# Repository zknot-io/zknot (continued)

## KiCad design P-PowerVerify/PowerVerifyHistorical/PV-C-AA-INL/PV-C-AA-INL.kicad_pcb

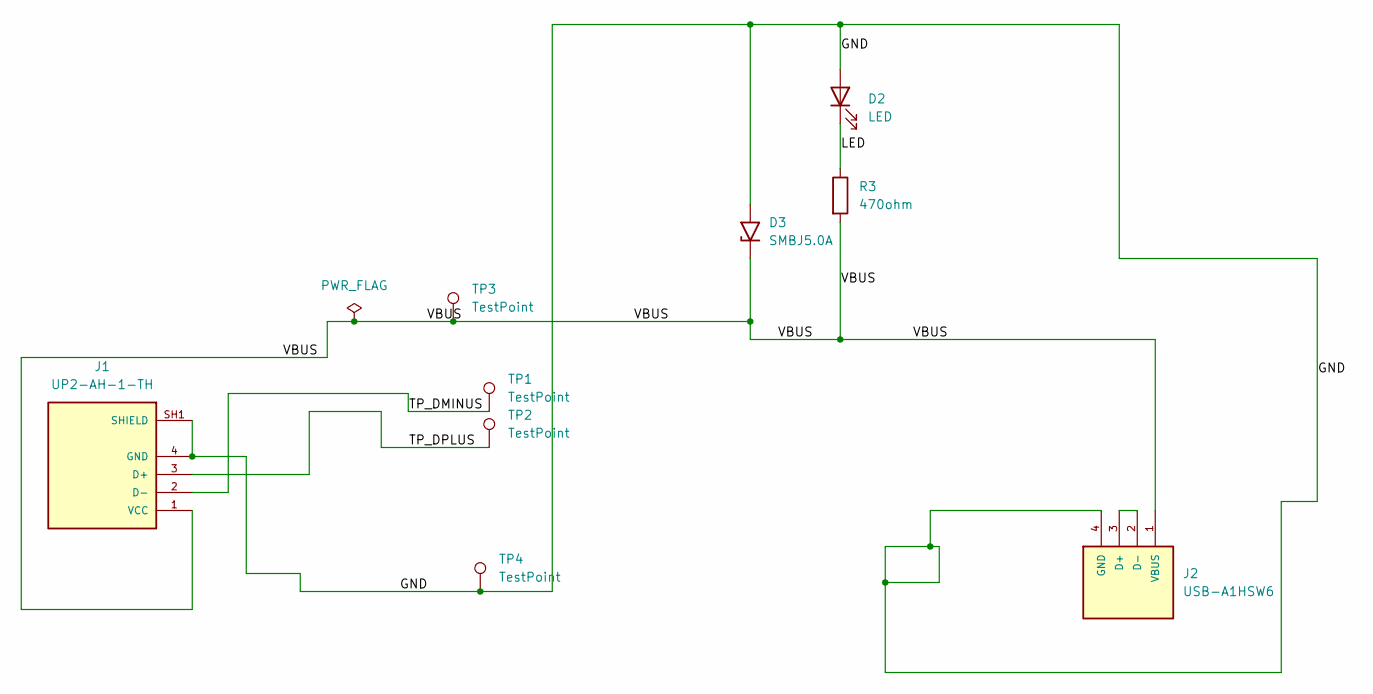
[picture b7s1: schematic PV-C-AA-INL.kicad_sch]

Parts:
D2: LED; LED_0603_1608Metric
D3: SMBJ5.0A; D_SMB
J1: UP2-AH-1-TH; CUI_UP2-AH-1-TH; PARTREV 1.05; DigiKey_Part_Number 102-3996-ND
J2: USB-A1HSW6; OST_USB-A1HSW6; PARTREV A; DigiKey_Part_Number ED2989-ND
R3: 470ohm; R_0402_1005Metric
TP1, TP2, TP3, TP4: TestPoint; TestPoint_Pad_D1.5mm

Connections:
/GND: D2.2 (A), D3.2 (A2), J1.4 (GND), J1.SH1 (SHIELD), J1.SH2 (SHIELD), J2.4 (GND), TP4.1
/LED: D2.1 (K), R3.1
/TP_DMINUS: J1.2 (D-), TP1.1
/TP_DPLUS: J1.3 (D+), TP2.1
/VBUS: D3.1 (A1), J1.1 (VCC), J2.1 (VBUS), R3.2, TP3.1
unnamed: J2.2 (D-), J2.3 (D+)

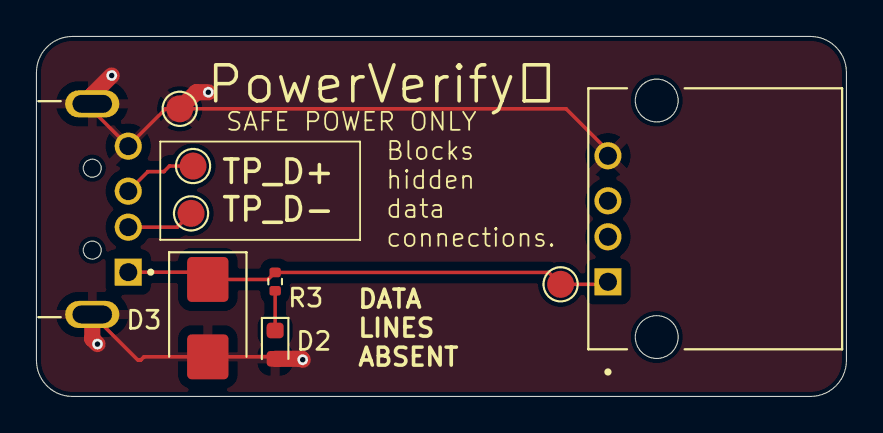
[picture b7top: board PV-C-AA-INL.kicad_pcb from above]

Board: 2 copper layers, 45.0 x 20.0 mm, 9 parts (0 on the bottom side), 6 nets.

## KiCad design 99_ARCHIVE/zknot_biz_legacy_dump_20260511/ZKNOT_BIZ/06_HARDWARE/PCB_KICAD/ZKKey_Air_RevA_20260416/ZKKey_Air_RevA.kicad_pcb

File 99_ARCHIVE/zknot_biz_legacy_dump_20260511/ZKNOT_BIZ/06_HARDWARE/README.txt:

ZKNOT / 06_HARDWARE
====================
Hardware design files, BOMs, and hardware master documents.

SUBFOLDERS:
  PCB_KICAD/  — KiCad project files (.zip per board revision)
  GERBERS/    — Fabrication Gerber files (.zip per board revision)
  BOM/        — Bills of materials (.xlsx)
  HW_DOCS/    — Hardware master documents (.docx)

CANONICAL FILES:
  ZKNOT_BOM-001_ZKM001_assembly_kit_20260301.xlsx
  ZKNOT_HW-001_ZKM001_hardware_firmware_master_20260301.docx
  ZKNOT_PCB-001_ZKM001_kicad_project_20260301.zip
  ZKNOT_PCB-001_ZKM001_gerbers_20260301.zip
  ZKNOT_PCB-002_PowerVerify_RevE_kicad_project_20260301.zip
  ZKNOT_PCB-002_PowerVerify_RevE_gerbers_20260301.zip
  ZKNOT_BOM-002_PowerVerify_RevE_bom_20260301.xlsx
  ZKNOT_DOC-010_device_id_registry_20260301.xlsx
  ZKNOT_HW-002_ZKKeyConnect_build1_wiring_doc_20260301.docx

TYPE CODES: BOM, HW, PCB

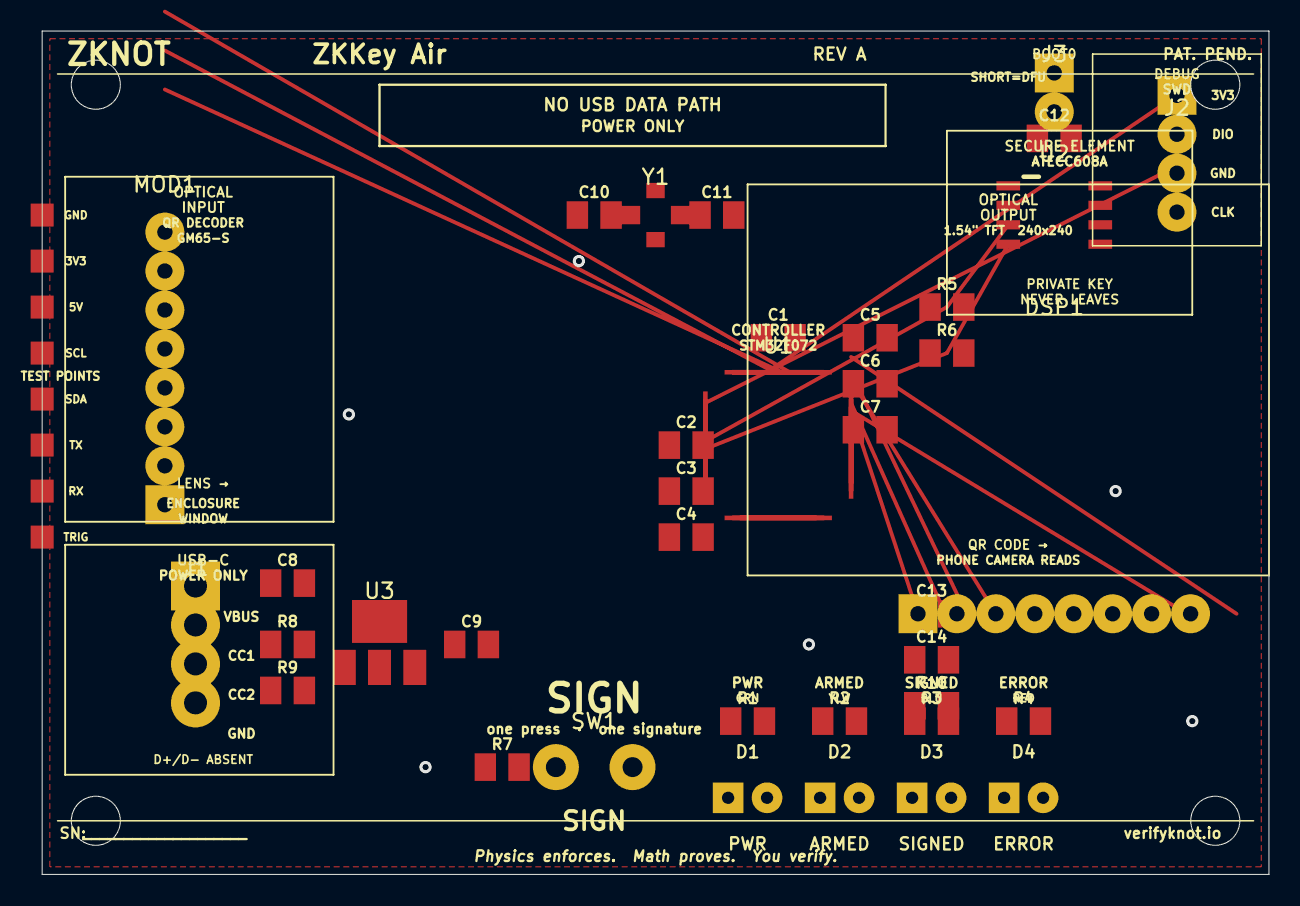
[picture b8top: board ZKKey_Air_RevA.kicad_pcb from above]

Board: 2 copper layers, 80.0 x 55.0 mm, 38 parts (0 on the bottom side), 26 nets.

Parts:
C1, C2, C3, C4, C5, C6, C7, C8, C9, C10, C11, C12, C13, C14: C_0805_2012Metric
D1: PWR; LED_D3.0mm
D2: ARMED; LED_D3.0mm
D3: SIGNED; LED_D3.0mm
D4: ERROR; LED_D3.0mm
DSP1: ST7789 TFT; PinHeader_1x08_P2.54mm_Vertical
J1: USB-C_PWR_ONLY; PinHeader_1x04_P2.54mm_Vertical
J2: SWD; PinHeader_1x04_P2.54mm_Vertical
J3: PinHeader_1x02_P2.54mm_Vertical
MOD1: GM65-S; PinHeader_1x08_P2.54mm_Vertical
R1, R2, R3, R4, R5, R6, R7, R8, R9, R10: R_0805_2012Metric
SW1: SIGN; SW_Tactile_SPST_Angled_PTS645
U1: STM32F072CBT6; LQFP-48_7x7mm_P0.5mm
U2: ATECC608A; SOIC-8_3.9x4.9mm_P1.27mm
U3: AMS1117-3.3; SOT-223-3_TabPin2
Y1: Crystal_SMD_3225-4Pin_3.2x2.5mm

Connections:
+3.3V: C2.1, C3.1, C4.1, C5.1, C6.1, C7.1, C9.1, C12.1, C13.1, C14.1, DSP1.2, J2.1, J3.2, MOD1.1, R5.1, R6.1, U1.1, U1.2, U1.9, U1.24, U1.48, U2.8, U3.2
+5V: C8.1, U3.3
ATEC_ALERT: U1.39, U2.2
BOOT0: J3.1, U1.44
BTN_PA0: R7.1, SW1.1, U1.10
CC1_5V1K: J1.2, R8.1
CC2_5V1K: J1.3, R9.1
GM65_TRIG: MOD1.5, U1.29
GND: C1.2, C2.2, C3.2, C4.2, C5.2, C6.2, C7.2, C8.2, C9.2, C10.2, C11.2, C12.2, C13.2, C14.2, D1.1, D2.1, D3.1, D4.1, DSP1.1, J1.4, J2.3, MOD1.2, R7.2, R8.2, R9.2, SW1.2, U1.8, U1.23, U1.47, U2.3, U3.1, Y1.3, Y1.4
I2C_SCL: R5.2, U1.42, U2.7
I2C_SDA: R6.2, U1.43, U2.5
LED_ARMED_PA2: D2.2, R2.1, R2.2, U1.12
LED_ERROR_PA6: D4.2, R4.1, R4.2, U1.16
LED_PWR_PA1: D1.2, R1.1, R1.2, U1.11
LED_SIGNED_PA3: D3.2, R3.1, R3.2, U1.13
NRST: C1.1, U1.7
SPI_MOSI: DSP1.4, U1.17
SPI_SCK: DSP1.3, U1.15
SWCLK: J2.4, U1.37
SWDIO: J2.2, U1.34
TFT_BL: DSP1.8, R10.1, R10.2, U1.21
TFT_CS: DSP1.7, U1.14
TFT_DC: DSP1.6, U1.26
TFT_RST: DSP1.5, U1.27
UART_RX: MOD1.3, U1.31
UART_TX: MOD1.4, U1.30

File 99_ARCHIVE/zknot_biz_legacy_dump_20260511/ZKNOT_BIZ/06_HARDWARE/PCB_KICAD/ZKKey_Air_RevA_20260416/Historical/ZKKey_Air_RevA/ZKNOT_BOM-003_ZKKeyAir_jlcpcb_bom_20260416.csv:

Comment,Designator,Footprint,LCSC Part #,Qty,Assembly,Notes
STM32F072CBT6,U1,Package_QFP:LQFP-48_7x7mm_P0.5mm,C81720,1,SMT,Reflow — same as Connect
ATECC608A-MAHDA-T,U2,Package_SO:SOIC-8_3.9x4.9mm_P1.27mm,C3395330,1,SMT,Reflow — same as Connect
AMS1117-3.3,U3,Package_TO_SOT_SMD:SOT-223-3_TabPin2,C6186,1,SMT,Reflow — 3.3V LDO
Crystal 8MHz,Y1,Crystal:Crystal_SMD_3225-4Pin_3.2x2.5mm,C9002,1,SMT,Reflow — HSE oscillator
100nF 0805,C1 C3 C4 C5 C12 C14,Capacitor_SMD:C_0805_2012Metric,C49678,6,SMT,Decoupling
10uF 0805,C2 C8 C9 C13,Capacitor_SMD:C_0805_2012Metric,C17024,4,SMT,Bulk decoupling — LDO and TFT
1uF 0805,C6,Capacitor_SMD:C_0805_2012Metric,C15849,1,SMT,VDDA bulk
10nF 0805,C7,Capacitor_SMD:C_0805_2012Metric,C57112,1,SMT,VDDA HF
12pF 0805,C10 C11,Capacitor_SMD:C_0805_2012Metric,C1557,2,SMT,Crystal load caps
270R 0805,R1 R2 R3 R4,Resistor_SMD:R_0805_2012Metric,C17630,4,SMT,LED current limit 270Ω
4.7k 0805,R5 R6,Resistor_SMD:R_0805_2012Metric,C23162,2,SMT,I2C pull-ups
10k 0805,R7,Resistor_SMD:R_0805_2012Metric,C17414,1,SMT,Button pull-down
5.1k 0805,R8 R9,Resistor_SMD:R_0805_2012Metric,C23186,2,SMT,USB-C CC1/CC2 pull-downs
10R 0805,R10,Resistor_SMD:R_0805_2012Metric,C17561,1,SMT,TFT backlight current limit
GM65-S QR Decoder Module,MOD1,Connector_PinHeader_2.54mm:PinHeader_1x08_P2.54mm_Vertical,,1,THT,Source: Handheld Scientific GM65-S or Grow GM65 — UART 3.3V — 30x17mm module — mount lens toward enclosure window
ST7789 1.54in 240x240 TFT,DSP1,Connector_PinHeader_2.54mm:PinHeader_1x08_P2.54mm_Vertical,,1,THT,Source: AliExpress/Adafruit 1.54in 240x240 SPI ST7789 module — GND VCC SCL SDA RES DC CS BL pinout — display face up through enclosure window
LED 3mm Green,D1,LED_THT:LED_D3.0mm,,1,THT,PWR — source locally
LED 3mm Yellow,D2,LED_THT:LED_D3.0mm,,1,THT,ARMED — source locally
LED 3mm Blue,D3,LED_THT:LED_D3.0mm,,1,THT,SIGNED — source locally
LED 3mm Red,D4,LED_THT:LED_D3.0mm,,1,THT,ERROR — source locally
Tactile Switch 6x6mm,SW1,Button_Switch_THT:SW_Tactile_SPST_Angled_PTS645,,1,THT,SIGN button — source locally
PinHeader 1x04 2.54mm,J2,Connector_PinHeader_2.54mm:PinHeader_1x04_P2.54mm_Vertical,,1,THT,SWD debug
PinHeader 1x02 2.54mm,J3,Connector_PinHeader_2.54mm:PinHeader_1x02_P2.54mm_Vertical,,1,THT,BOOT0 jumper
Jumper shunt 2.54mm,J3_shunt,,,,THT,BOOT0 shunt — keep one on board
USB-C Male Pigtail VBUS+GND+CC only,J1,Connector_PinHeader_2.54mm:PinHeader_1x04_P2.54mm_Vertical,,1,THT,4-wire only: VBUS CC1 CC2 GND — D+/D- wires MUST NOT BE CONNECTED — use pigtail with D+/D- physically cut or absent
M3 Standoff Nylon 10mm,H1 H2 H3 H4,MountingHole:MountingHole_3.2mm_M3,,4,THT,Enclosure mounting — match to enclosure standoff pattern

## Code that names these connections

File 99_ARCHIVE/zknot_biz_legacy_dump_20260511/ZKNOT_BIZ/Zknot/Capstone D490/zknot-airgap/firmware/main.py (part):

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

# ─── Pin config ───────────────────────────────────────────────────────────────
I2C_SDA       = 4
I2C_SCL       = 5
OLED_ADDR     = 0x3C
ATECC_ADDR    = 0x60
BUTTON_PIN    = 15
LED_PIN       = 25

UART_TX       = 0
UART_RX       = 1
SCANNER_TRIG  = 2

OLED_W        = 128
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# ─── Hardware init ────────────────────────────────────────────────────────────

def init():
    i2c = I2C(0, sda=Pin(I2C_SDA), scl=Pin(I2C_SCL), freq=100_000)
    oled = SSD1306_I2C(OLED_W, OLED_H, i2c, addr=OLED_ADDR)
    chip = ATECC608B(i2c, address=ATECC_ADDR)
    scanner = GM65Scanner(uart_id=0, tx_pin=UART_TX, rx_pin=UART_RX, trig_pin=SCANNER_TRIG)
    button = Pin(BUTTON_PIN, Pin.IN, Pin.PULL_UP)
    led = Pin(LED_PIN, Pin.OUT)
    return oled, chip, scanner, button, led
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
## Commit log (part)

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2026-04-18 init: ZKNOT business repo — April 2026
2026-04-18 feat: patents, firmware source, KM docs, journal — 2026-04-18
2026-04-22 Pre-reorganization snapshot — 2026-04-22
2026-04-22 Reorganize ZKNOT: merge 06_HARDWARE_FULL into 06_HARDWARE, unify bom/BOM and firmware/FIRMWARE case duplicates, renumber old-scheme 07/08/09/10/11 to match zip canonical scheme, move 11_RESUME to 00_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
2026-04-22 Add ZKNOT journal format template for future session summaries
2026-04-22 Validated: Pigtail_USB-C_4wire_ZKNOT symbol and footprint load cleanly in KiCad 10 (fixed semicolon-comments syntax error, bumped generator_version to 10.0)
2026-04-23 PowerVerify Rev 1: schematic complete, 3D render validated, ready for Windows DRC/track-width work
2026-04-24 PowerVerify Rev 1: Windows — added predefined track widths, DRC fixes
2026-05-02 Pre-migration baseline: track 00_COMMAND/ZKNOT_Organization_Handoff_20260427.md
    This commit establishes a clean rollback point before the v2 folder
    reorganization. The 00_COMMAND/ folder was previously untracked due
    to .gitignore excluding *.docx and *.pdf — only the markdown handoff
    is actually tracked here.
    Migration plan: see ZKNOT_KM-001_strategy_v2_20260502__ZK.docx
2026-05-02 Migration: merge fresh Drive export, quarantine superseded designs
    Sensitive files: 10 plaintext-on-disk files moved to encrypted
    vault at ~/ZKNOT_VAULT/sensitive_v3_20260502.tar.gz.age
    (bank PINs, identity docs, DD-214s, VA letter, payment processor
    recovery codes, credentials reference). Verified byte-perfect
    with SHA-256 hash comparison.
    Quarantined (out of canonical tree, in ~/ZKNOT_QUARANTINE/):
2026-05-02 v2 reorg: apply S-shop folder structure per KM-001 strategy
2026-05-04 journal: password manager consolidation 2026-05-04
2026-05-06 Capture thermal tamper indicator discovery
2026-05-07 PowerVerify mold v5 + cable shim — ready to print
2026-05-08 Production transition (evening): supplies, recipient prep, ship cycle for first 5 units
2026-05-11 Journal: SAM renewal with SDVOSB submitted
2026-05-11 Master docs v1.1: COO + CFO + SDVOSB strategy updated for post-VetCert state
    - COO-001: SDVOSB status PENDING→CERTIFIED, NAICS expanded to 8 codes,
    PSC expanded to 6 codes, LLC/Corporation ambiguity resolved, Section
    6 Contract Vehicle Ladder updated, VA VIP registration elevated to
    critical next action, pre-exit cleanup section added.
    - CFO-001: SDVOSB cert in data room (DONE), GAAP compliance notes
    added (DFARS attestation), valuation premium realized.
2026-05-11 Sort Downloads cleanup: federal letters, NDA templates, journals, KM, hardware/software handoffs
    - 9_GOV/federal/: UCP/VetCert approval letters
    - JAG/CONTRACTS/NDA/templates/: NDA v1.0 set (unilateral, mutual, demo, cheat sheet)
    - 3_OPS/journal/: production transition + session journals + cheatsheets
    - 3_OPS/km/: SOP-001, KM-002 acquisition prep, social presence handoffs
    - 6_SIG/hw/: PowerVerify rev1 completion + PUF integration handoffs
    - 6_SIG/sw/: SW-001 software master
2026-05-11 Remove lizhoke.com from ZKNOT vault — personal project, moved to ~/personal/
2026-05-12 Journal: ATECC provisioning path locked — Pi 5 + cryptoauthlib + Saleae
2026-05-12 Journal: pivots today, MCP2221A path locked, waiting on hardware
2026-05-16 docs(mfg): PV labeling decision record v3 — PAT-002-only, internal/external split, text-legible pot target
2026-05-16 Journal: PV labeling v3 locked, three units (PV1-00042/43/44) potted, awaiting 48hr cure
2026-05-16 Recover virgin-check script from Pico CIRCUITPY drive
2026-05-16 Add README for recovered Pico virgin check script
2026-05-16 Journal: Amazon MCP2221A clones DOA, Pico setup restored, decision deferred
2026-05-16 Plan: ZKNOT-PLAN-INFRA-001 — 3-month infrastructure buildout reference (Tier 1 default)
2026-05-16 Plan: ZKNOT-PLAN-SDVOSB-001 — SDVOSB procurement, surplus, and compliance reference
2026-05-16 Journal: Infra & SDVOSB strategic planning session — Tier 1 bootstrap, ~40 tasks added
2026-05-16 Finishing workstation + Graip strategy + coatings
2026-05-17 journal: ecosystem state after .org launch + .io routing pass
2026-05-18 journal: ecosystem state + procedures.zknot.org plan
2026-05-18 journal: add ecosystem state + thread-handoff doc
2026-05-18 journal: SOP backlog with dependency-ordered phases
2026-05-19 journal: first ZK signing — ZK-EW6E-EERX device, KAM6-M30B-4JHP first artifact
2026-05-19 journal: lesson — software first, hardware later
2026-05-19 DECISIONS_pv_labeling v3.1 addendum: per-unit ZK numbers
2026-05-19 ops: add KiCad ignores under 7_ENG/hw/
2026-05-19 hw: scaffold product family directories with READMEs
2026-05-19 hw/libs: add PowerVerify pigtail symbol + footprint (USB-C 4-wire THT arc, patent-002)
2026-05-19 ops: move capture_puf.sh into 6_SIG/ where it belongs
2026-05-20 journal(2026-05-20): v0.3.0 deploy + first verified unit
2026-05-21 journal(2026-05-20): comprehensive session handoff document
2026-05-21 Journal: ATECC pivot to Trust&GO + portfolio strategy
2026-05-21 Journal: ATECC bridge pivot to FT260 after rounin's notes
2026-05-22 journal(2026-05-21): PUF capture + post-pot sign 43/44/45
2026-05-22 journal(2026-05-21): small PCB QR labels + pot-survivability test setup
2026-05-22 2026-05-22: QR-pot labels journal + Hashstamp build journal + handoff
2026-05-23 Journal: PCB debug findings + revenue-first pivot
2026-05-23 journal: self-hosted checkout decisions
2026-05-23 Reddit karma + ATECC608B outreach post ideas
2026-05-23 journal: 2026-05-22 GovCon calendar prep
2026-05-23 Journal: bizdev event triage + NAICS selection
2026-05-23 Journal: 2026-05-02 KM migration & v2 reorg session
2026-05-23 Add password manager consolidation journal 2026-05-04
2026-05-23 journal: KiCad setup, hw structure, GRAIP intake (2026-05-22)
2026-05-23 Journal: Full infrastructure thread capture (pre-trip brain dump)
2026-05-23 journal: LinkedIn Featured + PUF article
2026-05-23 journal: full KM/PM session capture (so originating chat can be deleted)
2026-05-23 Journal: full session capture (SAM renewal, master docs v1.1, Downloads cleanup, open loops)
2026-05-23 Add marketing push battle plan journal
2026-05-23 PowerVerify new rev: design review, eFuse, comparator, validation
2026-05-23 journal: evidence-integrity SBIR reframe
2026-05-28 journal: income portfolio strategy + CMMC note on scan decision
2026-05-28 journal: trust model + SBIR scan decision + income strategy (pre-June 3)
2026-05-29 journal: outreach campaign + site deploy + audit
2026-05-29 journal: file entries from Downloads triage
2026-05-29 journal: downloads triage + zk-sort tool
2026-05-29 journal: protocol+docs pages shipped, concepts load
2026-05-29 journal: network printer setup (HP M478f, driverless IPP)
2026-05-29 journal: deploy path correction — Worker not Pages
2026-05-29 journal: deploy path resolved (Worker), deployed
2026-05-29 journal: verified live 614a2956
2026-05-29 km: 3-tier standard (INDEX + templates + systems/zknot-site); dedupe + archive dead journal tool
2026-05-29 gitignore: exclude 01_PATENTS (backed up off-repo)
2026-05-29 journal: verify trust-model review — both hero claims theater, HSM-blocked, sequencing recorded
2026-05-29 RPD bear thesis research + SA application submitted + coverage sequence locked
2026-05-29 journal: SDVOSB sole-source (19.1406) parked pending signing capability
2026-05-29 LYNX profile session: journal + systems note
2026-05-29 journal+km+ref: PUF/FRE/procurement personal monopoly thesis
2026-05-29 Add post-SBIR funding strategy journal + funding-vehicles systems note
2026-05-29 journal: comprehensive thread closeout — ecosystem build session
2026-05-29 journal: ZKKey Connect Rev 0 + software signer pivot — first ZK signing operational
2026-05-29 journal: provisioning architecture & decisions locked
2026-05-30 journal: exit strategy + SBIR dead
2026-05-30 journal: cmmc overview + priority triage (2026-05-29)
2026-05-31 ft260: first light — 6 parts verified, Path A HAL confirmed
2026-05-31 tier0: self-assert provisioning recipe (pre-lock, no secrets)
2026-05-31 ops: add fi-8170 scan→OCR wrapper
2026-06-01 Journal: 2026-06-01 centralized storage live + NAS plan reworked
2026-06-01 Add root context primer
2026-06-01 Add root primer + FT260 provisioning project primer
2026-06-01 tier0: provisioning recipe + ft260 systems doc + first-light journal (pre-lock)
2026-06-01 tier0: provisioning recipe (non-secret, pre-lock)
2026-06-01 atecc ledger: part 1 (012337d1) config-locked + keyed, pre-data-lock
2026-06-01 atecc ledger: part 1 complete — data-locked, testsig PASS
2026-06-02 atecc ledger: correct part 1 — data_lock + testsig PASS (sed failed earlier)
2026-06-02 atecc ledger: restore full pubkey for part 1
2026-06-02 FT260 primer: recipe proven; add primer-system handoff
2026-06-02 atecc ledger: part 2 (0123fc0b) complete
2026-06-02 atecc ledger: part 3 (01231e45) complete
2026-06-02 atecc ledger: part 4 (0123c9ea) complete — batch of 4 done
2026-06-02 journal + systems: ft260 batch provisioning, proven sequence
2026-06-03 checkpoint before filing-system remap
2026-06-09 ZKKey v1: PAT-020 strong-form gate + addendum; capability spec v5 (B-split, U585+OPTIGA); firmware enforcement (gate #3); verifier spec + time-binding decision; architecture map; journal (2026-06-08)
2026-06-09 verifyknot primer v2 (honest re-level); CubeMX TZ bring-up primer; journal 2026-06-09
2026-06-09 docs(systems): verifyknot primer v2 — honest two-state status
2026-06-09 Move root primer CONTEXT.md to repo root (re-entry keystone)
2026-06-09 reorg: P-/S- prefix scheme; function folders
2026-06-10 PAT-020/PAT-021 as-filed provisional specs (fonts embedded) + micro-entity certs
2026-06-11 P-ZKKEY/Attestor: carrier-r1 project skeleton, vendor CAD libs, datasheets
2026-06-13 provision: first Rev2-Attestor part 01234df5...547ee
2026-06-13 provision: seal data zone + clean record for 01234df5...547ee
2026-06-13 tooling: fail-closed record + bus auto-detect for attestor provisioning
2026-06-13 attestor: build/test SOP + functional-test verifier
2026-06-13 attestor firmware: working build (serial str fix), signs on RP2350/CP10.2
2026-06-13 journal: verifyknot /start live-device verification
2026-06-15 journal: seed-r1 review resolved — ATECC decoupling + island-net miswire caught by netlist trace, fixed end to end
2026-06-15 refactor: promote Attestor to top-level P-Attestor; remove from P-ZKKEY/Attestor
2026-06-15 chore: remove PowerVerifyHistorical (embedded-repo files; archived to 99_ARCHIVE, originals retained off-vault)
2026-06-19 Track WitnessMark KiCad project (was untracked)
2026-06-19 WitnessMark: fix VDDA cap shorting GND to +3V3 (rail merge); GND now distinct
2026-06-19 gitignore KiCad derived/cache files
2026-06-19 Restore VDDA decoupling (C8/C9), crystal caps to 18pF, assign J5 footprint
2026-06-19 Restore VDDA decoupling (C8/C9), crystal caps 18pF, J5 verified GCT footprint
2026-06-20 WitnessMark schematic: BOOT0/J3 grounds, USB Rs 0R, SWD direct
2026-06-20 WitnessMark schematic: BOOT0/J3 grounds, all caps grounded, USB Rs 0R, SWD direct, crystal 18pF
2026-06-22 WitnessMark PCB: crystal/OPTIGA/USB routed, GND pour
2026-06-22 WitnessMark PCB: routed board, 418 segments (promoted from recovery copy)
2026-06-23 WitnessMark-2 PCB: restored 389-seg routing from .history after crash
2026-06-23 WitnessMark-2: restore point before untitled-orphan removal
2026-06-24 provision: 3x ATECC608B -> Rev2-Attestor (rows 6-8, all PASS, 128-char pubkeys)
2026-06-24 fw(seed-r1): XIAO RP2040 signer ported from Pico; pins locked from netlist + bring-up doc
2026-06-24 fix(seed-r1): repo code.py was stale Pico file; replace with XIAO port (board.SDA)
2026-06-24 journal: 2026-06-24 seed-r1 firmware bring-up to first verified signature
2026-06-24 fix(sign): rebuild BUNDLED_PUBKEYS from ledger (lowercase keys+lookup, all 8 enrolled chips); row 7 now issues
2026-06-24 provision: 2x ATECC608B -> Rev2-Attestor (rows 9-10, all PASS)
2026-06-27 Add Attestor seed-r1 unit-build + label-print ledger (first 3 commercial units)
